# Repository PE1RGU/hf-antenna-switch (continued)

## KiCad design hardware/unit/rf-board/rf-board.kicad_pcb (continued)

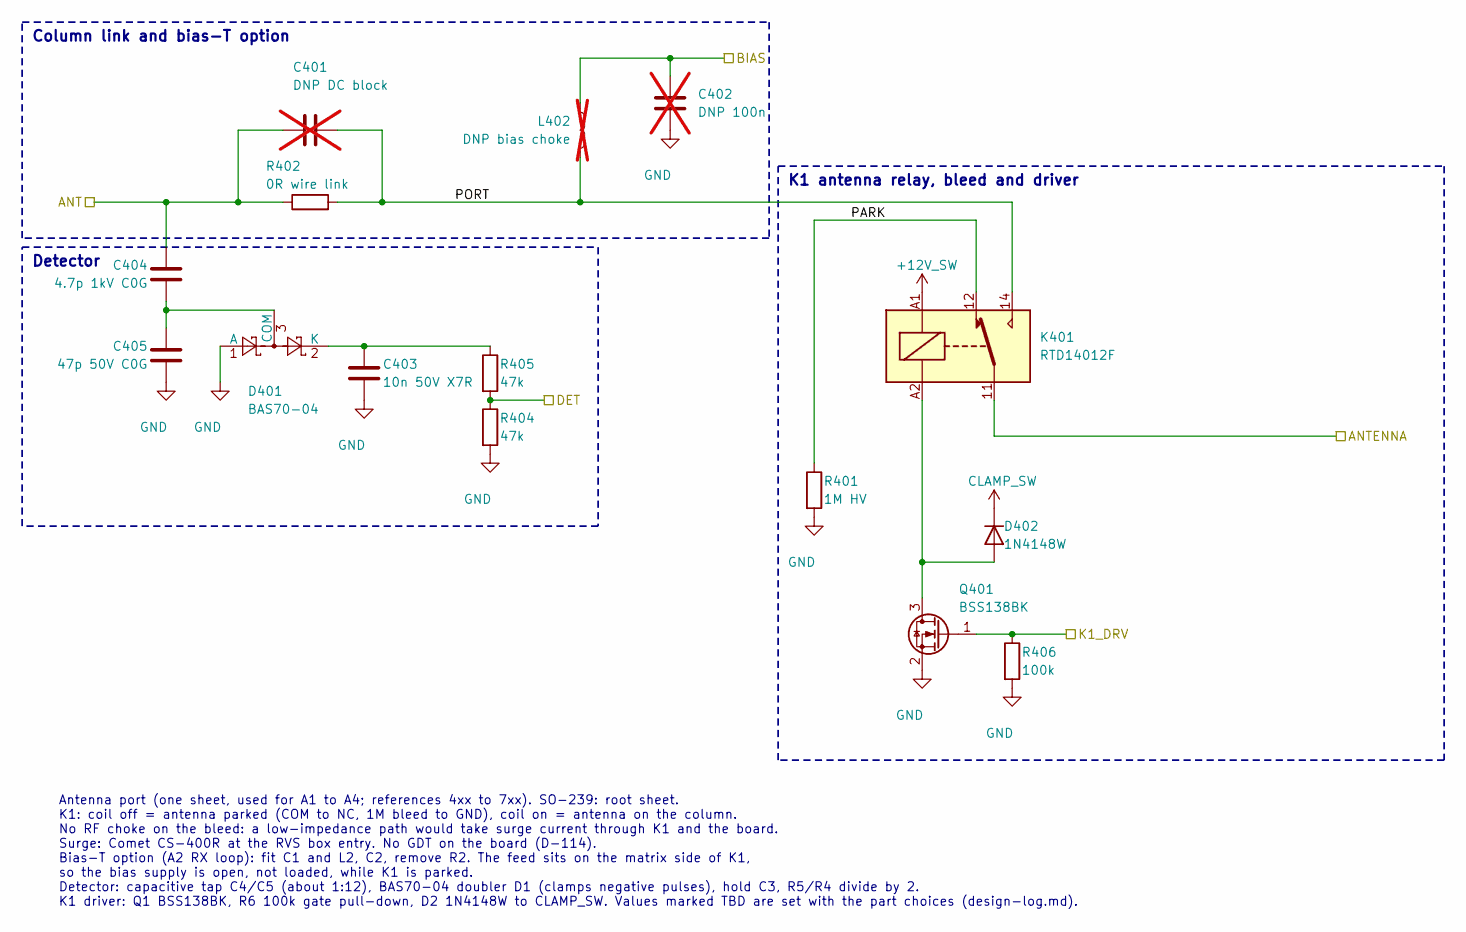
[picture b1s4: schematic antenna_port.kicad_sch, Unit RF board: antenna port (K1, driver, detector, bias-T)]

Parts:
C401: DNP DC block; C_1812_4532Metric_Pad1.57x3.40mm_HandSolder; not fitted
C402: DNP 100n; C_1206_3216Metric_Pad1.33x1.80mm_HandSolder; not fitted
C403: 10n 50V X7R; C_0603_1608Metric_Pad1.08x0.95mm_HandSolder
C404: 4.7p 1kV C0G; C_1206_3216Metric_RFgap2.0; MPN 1206J1K04P70CCT
C405: 47p 50V C0G; C_0603_1608Metric_Pad1.08x0.95mm_HandSolder
D401: BAS70-04; SOT-23; MPN BAS70-04
D402: 1N4148W; D_SOD-123; MPN 1N4148W
K401: RTD14012F; Relay_SPDT_Schrack-RT1-16A-FormC_RM5mm; MPN RTD14012F
L402: DNP bias choke; L_1812_4532Metric_Pad1.30x3.40mm_HandSolder; not fitted
Q401: BSS138BK; SOT-23; MPN BSS138BK,215
R401: 1M HV; R_Axial_DIN0207_L6.3mm_D2.5mm_P10.16mm_Horizontal
R402: 0R wire link; WireLink_P7.62mm_D1.0mm
R404, R405: 47k; R_0603_1608Metric_Pad0.98x0.95mm_HandSolder
R406: 100k; R_0603_1608Metric_Pad0.98x0.95mm_HandSolder

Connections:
+12V_SW: K401.A1; also elsewhere on the board
/A1_ANTENNA: K401.11; also elsewhere on the board
/A1_BIAS: C402.1, L402.1; also elsewhere on the board
/A1_DET: R404.1, R405.2; also elsewhere on the board
/A1_K1_DRV: Q401.1 (G), R406.1; also elsewhere on the board
/ANT1: C401.1, C404.1, R402.1; also elsewhere on the board
/Antenna port A1/PARK: K401.12, R401.1
/Antenna port A1/PORT: C401.2, K401.14, L402.2, R402.2
CLAMP_SW: D402.1 (K); also elsewhere on the board
GND: C402.2, C403.2, C405.2, D401.1 (A), Q401.2 (S), R401.2, R404.2, R406.2; also elsewhere on the board
unnamed: C404.2, C405.1, D401.3 (COM)
unnamed: C403.1, D401.2 (K), R405.1
unnamed: D402.2 (A), K401.A2, Q401.3 (D)

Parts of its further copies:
C501, C601, C701: DNP DC block; C_1812_4532Metric_Pad1.57x3.40mm_HandSolder; not fitted
C502, C602, C702: DNP 100n; C_1206_3216Metric_Pad1.33x1.80mm_HandSolder; not fitted
C503, C603, C703: 10n 50V X7R; C_0603_1608Metric_Pad1.08x0.95mm_HandSolder
C504, C604, C704: 4.7p 1kV C0G; C_1206_3216Metric_RFgap2.0; MPN 1206J1K04P70CCT
C505, C605, C705: 47p 50V C0G; C_0603_1608Metric_Pad1.08x0.95mm_HandSolder
D501, D601, D701: BAS70-04; SOT-23; MPN BAS70-04
D502, D602, D702: 1N4148W; D_SOD-123; MPN 1N4148W
K501, K601, K701: RTD14012F; Relay_SPDT_Schrack-RT1-16A-FormC_RM5mm; MPN RTD14012F
L502, L602, L702: DNP bias choke; L_1812_4532Metric_Pad1.30x3.40mm_HandSolder; not fitted
Q501, Q601, Q701: BSS138BK; SOT-23; MPN BSS138BK,215
R501, R601, R701: 1M HV; R_Axial_DIN0207_L6.3mm_D2.5mm_P10.16mm_Horizontal
R502, R602, R702: 0R wire link; WireLink_P7.62mm_D1.0mm
R504, R505, R604, R605, R704, R705: 47k; R_0603_1608Metric_Pad0.98x0.95mm_HandSolder
R506, R606, R706: 100k; R_0603_1608Metric_Pad0.98x0.95mm_HandSolder

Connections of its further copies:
+12V_SW: K501.A1, K601.A1, K701.A1; also elsewhere on the board
/A2_ANTENNA: K501.11; also elsewhere on the board
/A2_BIAS: C502.1, L502.1; also elsewhere on the board
/A2_DET: R504.1, R505.2; also elsewhere on the board
/A2_K1_DRV: Q501.1 (G), R506.1; also elsewhere on the board
/A3_ANTENNA: K601.11; also elsewhere on the board
/A3_BIAS: C602.1, L602.1; also elsewhere on the board
/A3_DET: R604.1, R605.2; also elsewhere on the board
/A3_K1_DRV: Q601.1 (G), R606.1; also elsewhere on the board
/A4_ANTENNA: K701.11; also elsewhere on the board
/A4_BIAS: C702.1, L702.1; also elsewhere on the board
/A4_DET: R704.1, R705.2; also elsewhere on the board
/A4_K1_DRV: Q701.1 (G), R706.1; also elsewhere on the board
/ANT2: C501.1, C504.1, R502.1; also elsewhere on the board
/ANT3: C601.1, C604.1, R602.1; also elsewhere on the board
/ANT4: C701.1, C704.1, R702.1; also elsewhere on the board
/Antenna port A2/PARK: K501.12, R501.1
/Antenna port A2/PORT: C501.2, K501.14, L502.2, R502.2
/Antenna port A3/PARK: K601.12, R601.1
/Antenna port A3/PORT: C601.2, K601.14, L602.2, R602.2
/Antenna port A4/PARK: K701.12, R701.1
/Antenna port A4/PORT: C701.2, K701.14, L702.2, R702.2
CLAMP_SW: D502.1 (K), D602.1 (K), D702.1 (K); also elsewhere on the board
GND: C502.2, C503.2, C505.2, C602.2, C603.2, C605.2, C702.2, C703.2, C705.2, D501.1 (A), D601.1 (A), D701.1 (A), Q501.2 (S), Q601.2 (S), Q701.2 (S), R501.2, R504.2, R506.2, R601.2, R604.2, R606.2, R701.2, R704.2, R706.2; also elsewhere on the board
unnamed: C504.2, C505.1, D501.3 (COM)
unnamed: C503.1, D501.2 (K), R505.1
unnamed: D502.2 (A), K501.A2, Q501.3 (D)
unnamed: C604.2, C605.1, D601.3 (COM)
unnamed: C603.1, D601.2 (K), R605.1
unnamed: D602.2 (A), K601.A2, Q601.3 (D)
unnamed: C704.2, C705.1, D701.3 (COM)
unnamed: C703.1, D701.2 (K), R705.1
unnamed: D702.2 (A), K701.A2, Q701.3 (D)

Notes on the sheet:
Antenna port (one sheet, used for A1 to A4; references 4xx to 7xx). SO-239: root sheet. K1: coil off = antenna parked (COM to NC, 1M bleed to GND), coil on = antenna on the column. No RF choke on the bleed: a low-impedance path would take surge current through K1 and the board. Surge: Comet CS-400R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
Column link and bias-T option
Detector
K1 antenna relay, bleed and driver

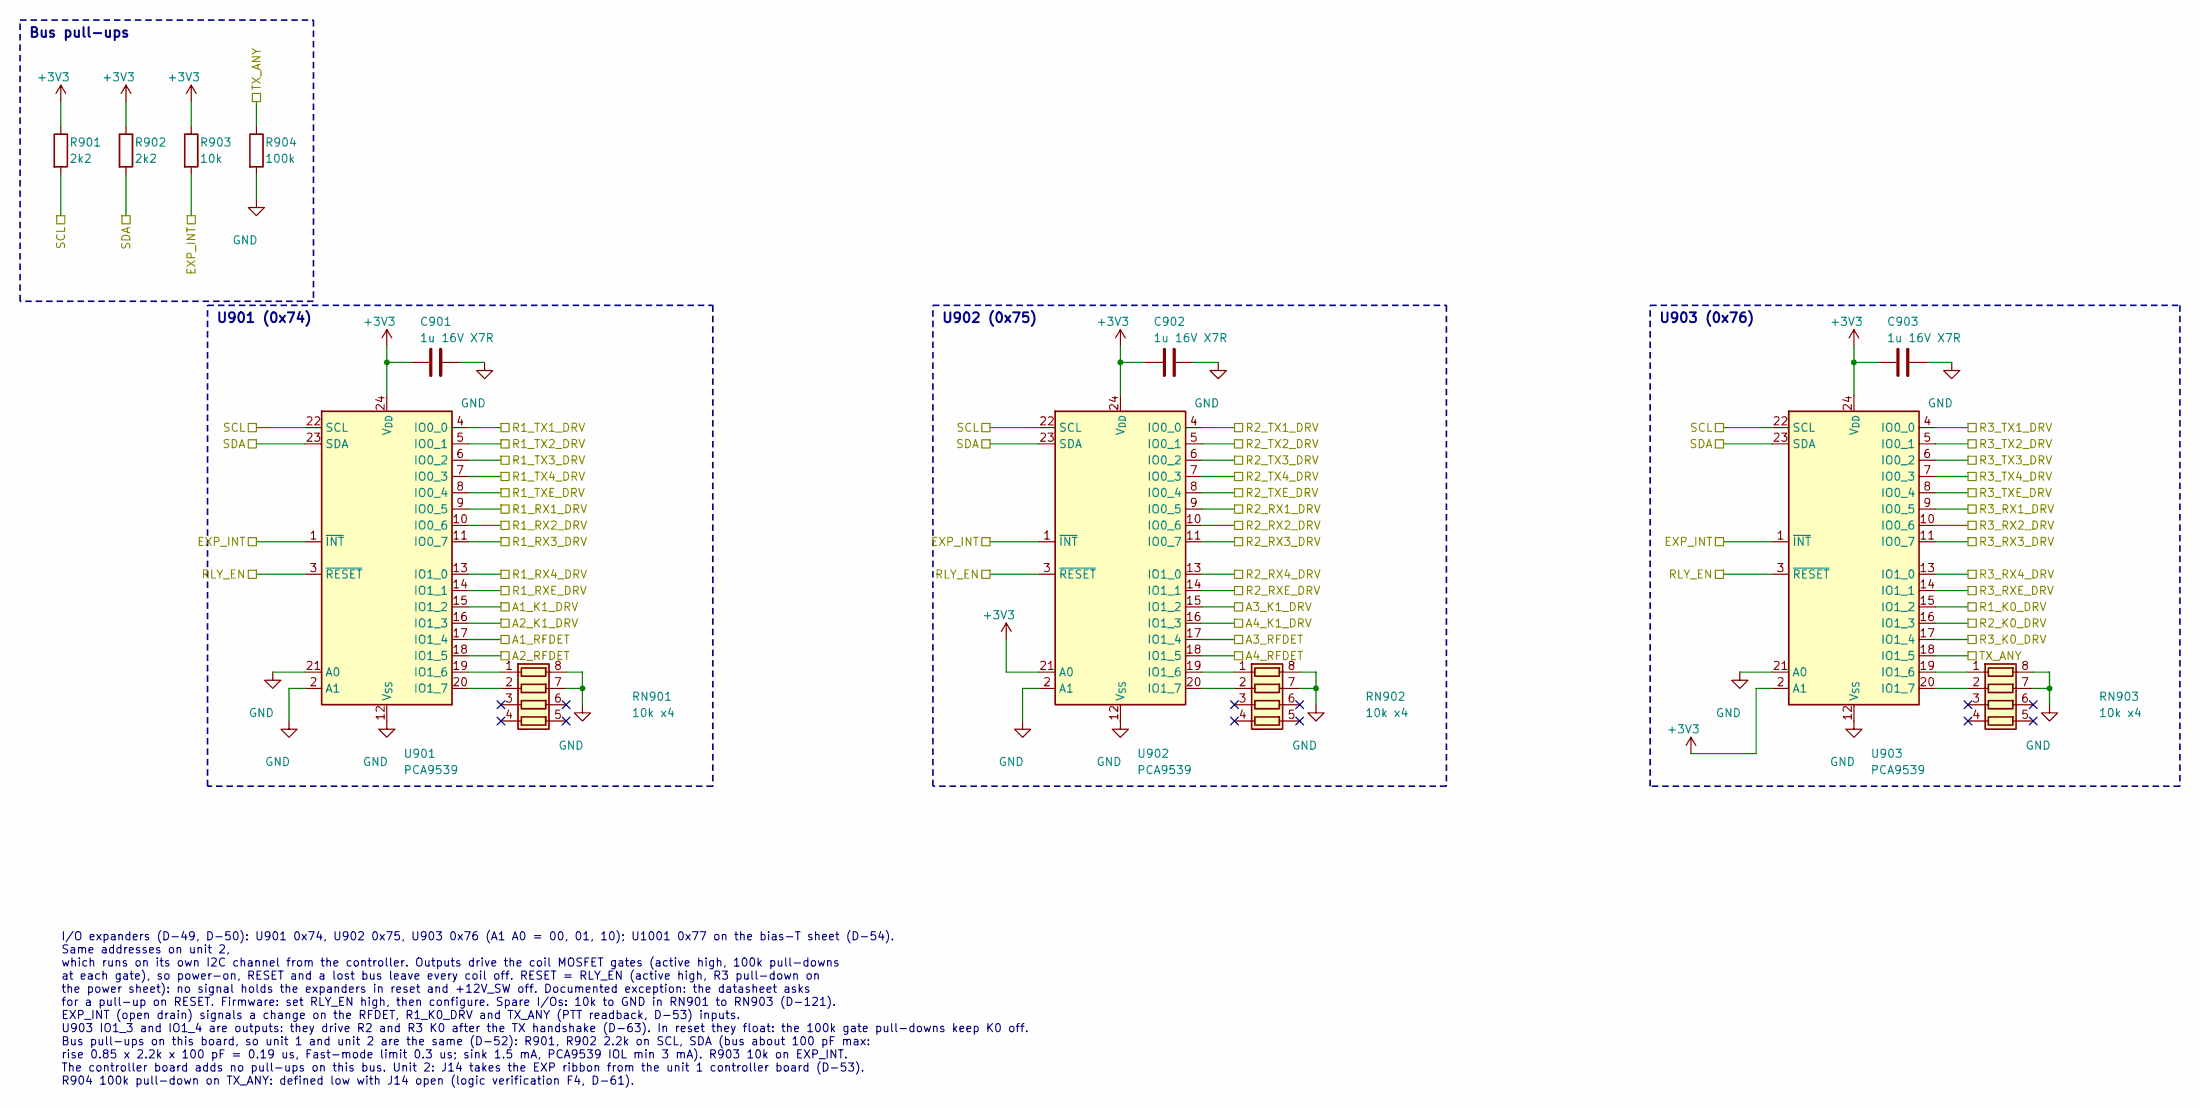
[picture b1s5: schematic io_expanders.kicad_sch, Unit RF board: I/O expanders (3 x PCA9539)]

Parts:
C901, C902, C903: 1u 16V X7R; C_0603_1608Metric_Pad1.08x0.95mm_HandSolder
R901, R902: 2k2; R_0603_1608Metric_Pad0.98x0.95mm_HandSolder
R903: 10k; R_0603_1608Metric_Pad0.98x0.95mm_HandSolder
R904: 100k; R_0603_1608Metric_Pad0.98x0.95mm_HandSolder
RN901, RN902, RN903: 10k x4; R_Array_Convex_4x0603; MPN CAY16-103J4LF
U901, U902, U903: PCA9539; TSSOP-24_4.4x7.8mm_P0.65mm; MPN PCA9539PW,118

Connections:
+3V3: C901.1, C902.1, C903.1, R901.1, R902.1, R903.1, U901.24 (V_{DD}), U902.21 (A0), U902.24 (V_{DD}), U903.2 (A1), U903.24 (V_{DD}); also elsewhere on the board
/A1_K1_DRV: U901.15 (IO1_2); also elsewhere on the board
/A2_K1_DRV: U901.16 (IO1_3); also elsewhere on the board
/A2_RFDET: U901.18 (IO1_5); also elsewhere on the board
/A3_K1_DRV: U902.15 (IO1_2); also elsewhere on the board
/A4_K1_DRV: U902.16 (IO1_3); also elsewhere on the board
/EXP_INT: R903.2, U901.1 (~INT), U902.1 (~INT), U903.1 (~INT); also elsewhere on the board
/IO expanders/A1_RFDET: U901.17 (IO1_4); also elsewhere on the board
/IO expanders/A3_RFDET: U902.17 (IO1_4); also elsewhere on the board
/IO expanders/A4_RFDET: U902.18 (IO1_5); also elsewhere on the board
/R1_K0_DRV: U903.15 (IO1_2); also elsewhere on the board
/R1_RX1_DRV: U901.9 (IO0_5); also elsewhere on the board
/R1_RX2_DRV: U901.10 (IO0_6); also elsewhere on the board
/R1_RX3_DRV: U901.11 (IO0_7); also elsewhere on the board
/R1_RX4_DRV: U901.13 (IO1_0); also elsewhere on the board
/R1_RXE_DRV: U901.14 (IO1_1); also elsewhere on the board
/R1_TX1_DRV: U901.4 (IO0_0); also elsewhere on the board
/R1_TX2_DRV: U901.5 (IO0_1); also elsewhere on the board
/R1_TX3_DRV: U901.6 (IO0_2); also elsewhere on the board
/R1_TX4_DRV: U901.7 (IO0_3); also elsewhere on the board
/R1_TXE_DRV: U901.8 (IO0_4); also elsewhere on the board
/R2_K0_DRV: U903.16 (IO1_3); also elsewhere on the board
/R2_RX1_DRV: U902.9 (IO0_5); also elsewhere on the board
/R2_RX2_DRV: U902.10 (IO0_6); also elsewhere on the board
/R2_RX3_DRV: U902.11 (IO0_7); also elsewhere on the board
/R2_RX4_DRV: U902.13 (IO1_0); also elsewhere on the board
/R2_RXE_DRV: U902.14 (IO1_1); also elsewhere on the board
/R2_TX1_DRV: U902.4 (IO0_0); also elsewhere on the board
/R2_TX2_DRV: U902.5 (IO0_1); also elsewhere on the board
/R2_TX3_DRV: U902.6 (IO0_2); also elsewhere on the board
/R2_TX4_DRV: U902.7 (IO0_3); also elsewhere on the board
/R2_TXE_DRV: U902.8 (IO0_4); also elsewhere on the board
/R3_K0_DRV: U903.17 (IO1_4); also elsewhere on the board
/R3_RX1_DRV: U903.9 (IO0_5); also elsewhere on the board
/R3_RX2_DRV: U903.10 (IO0_6); also elsewhere on the board
/R3_RX3_DRV: U903.11 (IO0_7); also elsewhere on the board
/R3_RX4_DRV: U903.13 (IO1_0); also elsewhere on the board
/R3_RXE_DRV: U903.14 (IO1_1); also elsewhere on the board
/R3_TX1_DRV: U903.4 (IO0_0); also elsewhere on the board
/R3_TX2_DRV: U903.5 (IO0_1); also elsewhere on the board
/R3_TX3_DRV: U903.6 (IO0_2); also elsewhere on the board
/R3_TX4_DRV: U903.7 (IO0_3); also elsewhere on the board
/R3_TXE_DRV: U903.8 (IO0_4); also elsewhere on the board
/RLY_EN: U901.3 (~RESET), U902.3 (~RESET), U903.3 (~RESET); also elsewhere on the board
/SCL: R901.2, U901.22 (SCL), U902.22 (SCL), U903.22 (SCL); also elsewhere on the board
/SDA: R902.2, U901.23 (SDA), U902.23 (SDA), U903.23 (SDA); also elsewhere on the board
/TX_ANY: R904.1, U903.18 (IO1_5); also elsewhere on the board
GND: C901.2, C902.2, C903.2, R904.2, RN901.7 (R2.2), RN901.8 (R1.2), RN902.7 (R2.2), RN902.8 (R1.2), RN903.7 (R2.2), RN903.8 (R1.2), U901.2 (A1), U901.12 (V_{SS}), U901.21 (A0), U902.2 (A1), U902.12 (V_{SS}), U903.12 (V_{SS}), U903.21 (A0); also elsewhere on the board
unnamed: RN901.1 (R1.1), U901.19 (IO1_6)
unnamed: RN901.2 (R2.1), U901.20 (IO1_7)
unnamed: RN902.1 (R1.1), U902.19 (IO1_6)
unnamed: RN902.2 (R2.1), U902.20 (IO1_7)
unnamed: RN903.1 (R1.1), U903.19 (IO1_6)
unnamed: RN903.2 (R2.1), U903.20 (IO1_7)

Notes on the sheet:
I/O expanders (D-49, D-50): U901 0x74, U902 0x75, U903 0x76 (A1 A0 = 00, 01, 10); U1001 0x77 on the bias-T sheet (D-54). Same addresses on unit 2, which runs on its own I2C channel from the controller. Outputs drive the coil MOSFET gates (active high, 100k pull-downs at each gate), so power-on, RES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
Bus pull-ups
U901 (0x74)
U902 (0x75)
U903 (0x76)

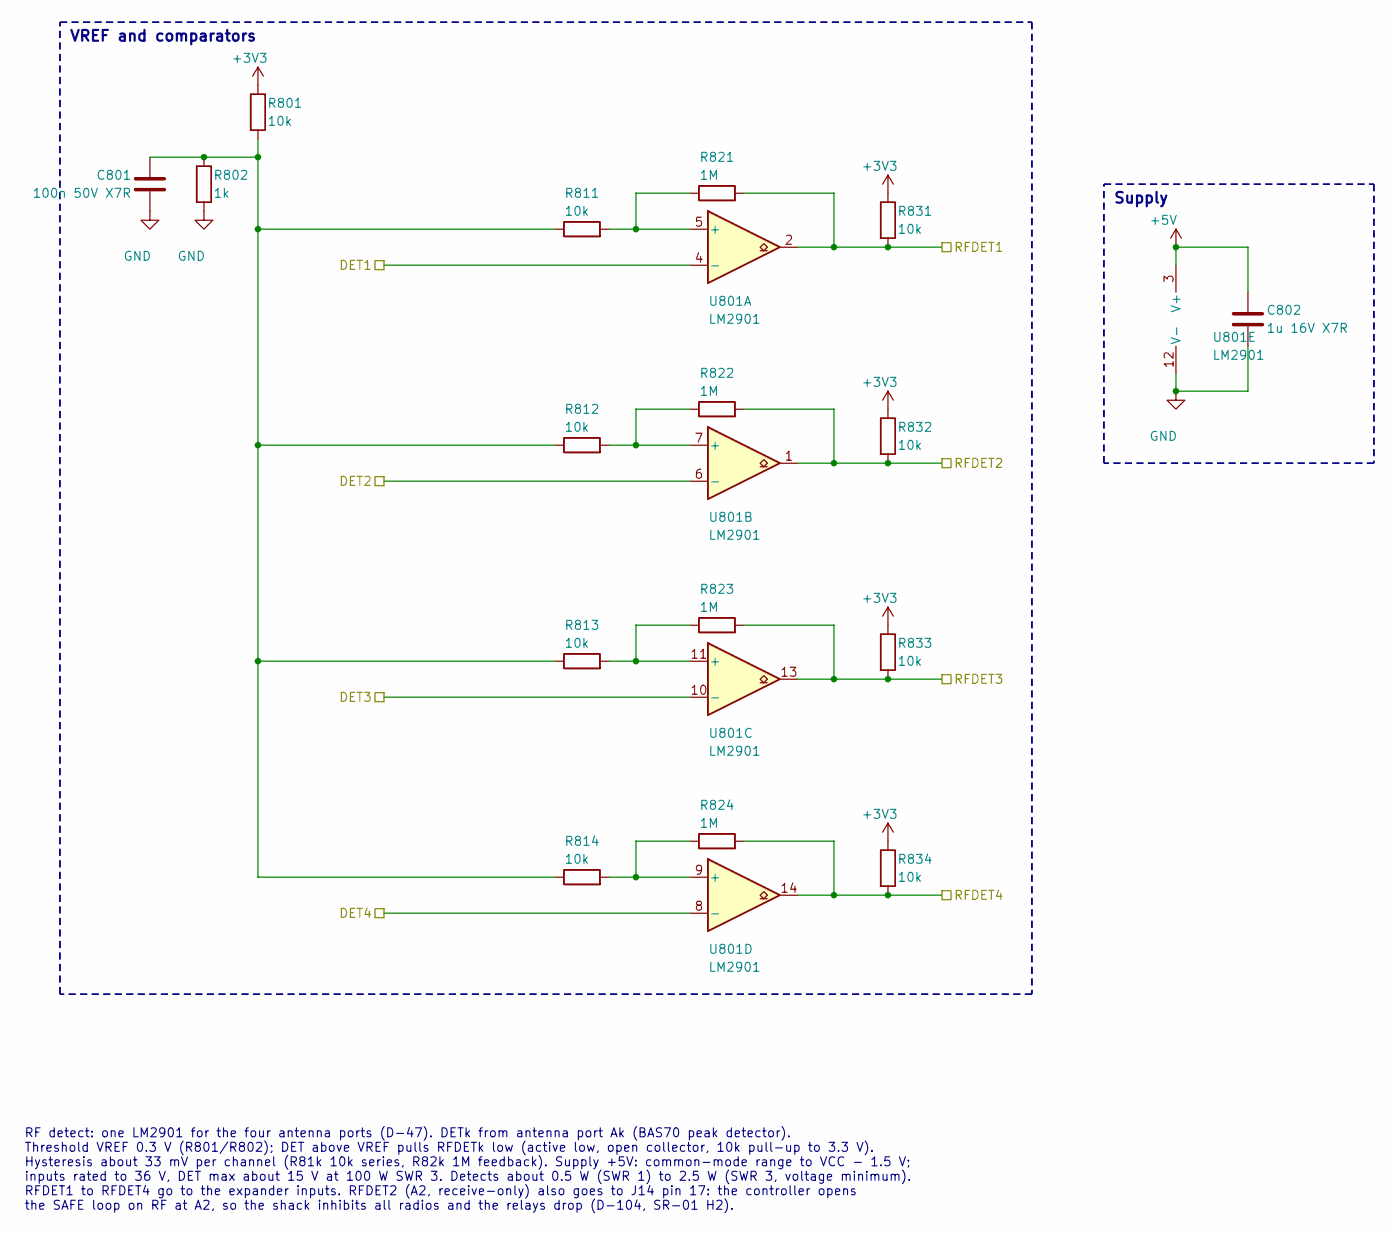
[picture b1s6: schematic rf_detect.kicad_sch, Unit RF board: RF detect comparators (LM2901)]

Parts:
C801: 100n 50V X7R; C_0603_1608Metric_Pad1.08x0.95mm_HandSolder
C802: 1u 16V X7R; C_0603_1608Metric_Pad1.08x0.95mm_HandSolder
R801, R811, R812, R813, R814, R831, R832, R833, R834: 10k; R_0603_1608Metric_Pad0.98x0.95mm_HandSolder
R802: 1k; R_0603_1608Metric_Pad0.98x0.95mm_HandSolder
R821, R822, R823, R824: 1M; R_0603_1608Metric_Pad0.98x0.95mm_HandSolder
U801: LM2901; SOIC-14_3.9x8.7mm_P1.27mm; MPN LM2901DR

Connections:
+3V3: R801.1, R831.1, R832.1, R833.1, R834.1; also elsewhere on the board
+5V: C802.1, U801.3 (V+); also elsewhere on the board
/A1_DET: U801.4 (-); also elsewhere on the board
/A2_DET: U801.6 (-); also elsewhere on the board
/A2_RFDET: R822.2, R832.2, U801.1; also elsewhere on the board
/A3_DET: U801.10 (-); also elsewhere on the board
/A4_DET: U801.8 (-); also elsewhere on the board
/IO expanders/A1_RFDET: R821.2, R831.2, U801.2; also elsewhere on the board
/IO expanders/A3_RFDET: R823.2, R833.2, U801.13; also elsewhere on the board
/IO expanders/A4_RFDET: R824.2, R834.2, U801.14; also elsewhere on the board
GND: C801.2, C802.2, R802.2, U801.12 (V-); also elsewhere on the board
unnamed: C801.1, R801.2, R802.1, R811.1, R812.1, R813.1, R814.1
unnamed: R811.2, R821.1, U801.5 (+)
unnamed: R812.2, R822.1, U801.7 (+)
unnamed: R813.2, R823.1, U801.11 (+)
unnamed: R814.2, R824.1, U801.9 (+)

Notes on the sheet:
RF detect: one LM2901 for the four antenna ports (D-47). DETk from antenna port Ak (BAS70 peak detector). Threshold VREF 0.3 V (R801/R802); DET above VREF pulls RFDETk low (active low, open collector, 10k pull-up to 3.3 V). Hysteresis about 33 mV per channel (R81k 10k series, R82k 1M feedback). Sup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
VREF and comparators
Supply

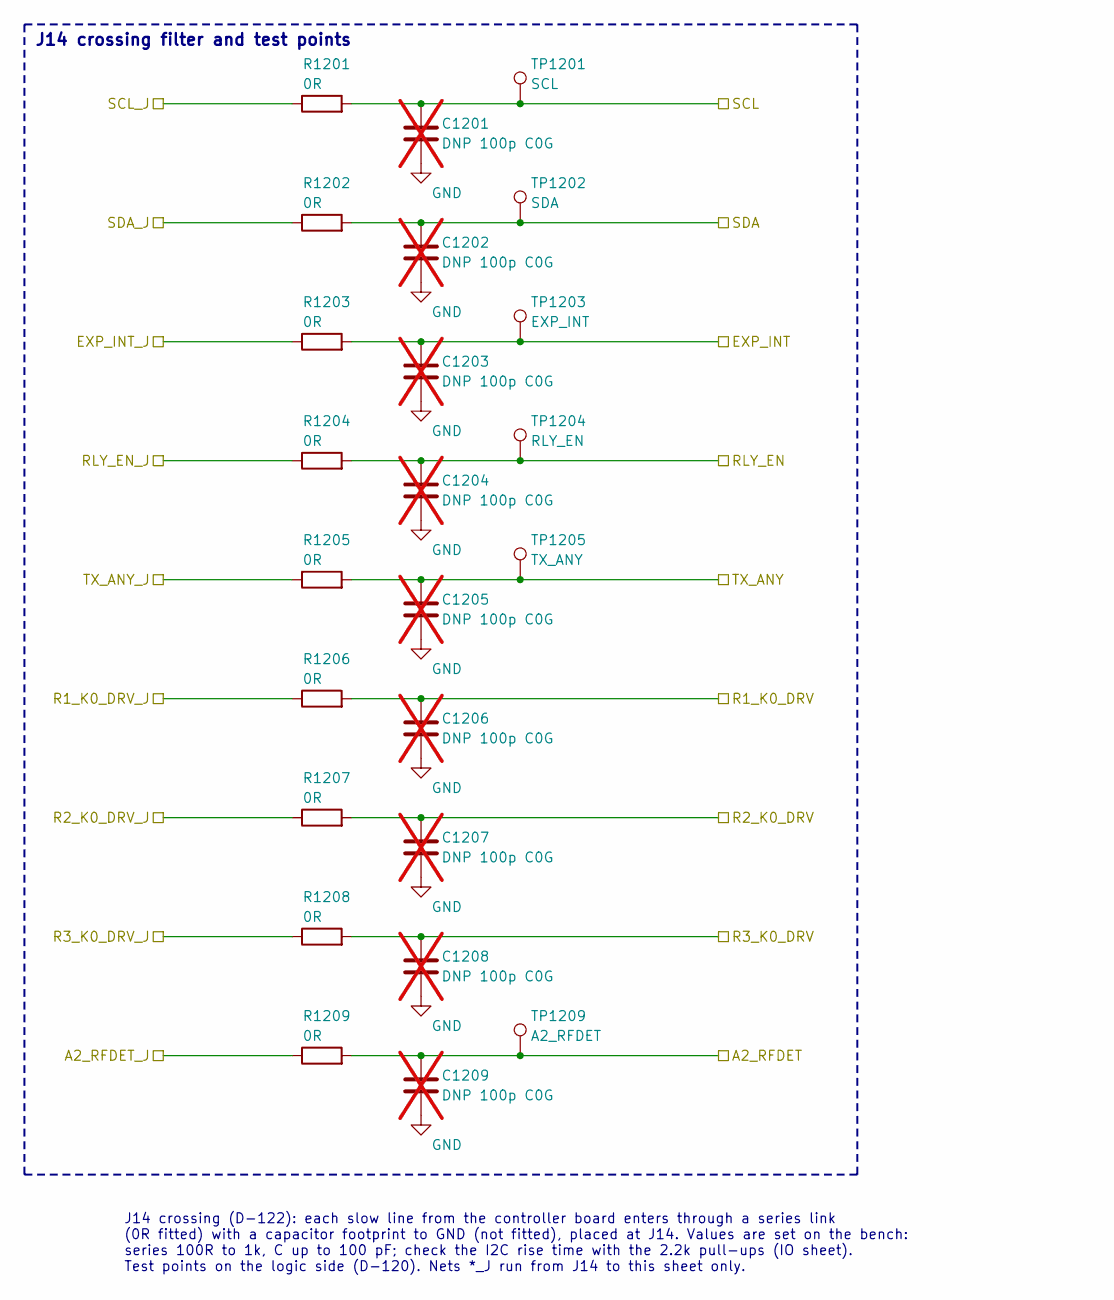
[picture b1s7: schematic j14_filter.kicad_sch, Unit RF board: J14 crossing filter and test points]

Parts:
C1201, C1202, C1203, C1204, C1205, C1206, C1207, C1208, C1209: DNP 100p C0G; C_0603_1608Metric_Pad1.08x0.95mm_HandSolder; not fitted
R1201, R1202, R1203, R1204, R1205, R1206, R1207, R1208, R1209: 0R; R_0603_1608Metric_Pad0.98x0.95mm_HandSolder
TP1201: SCL; TestPoint_Pad_D1.5mm
TP1202: SDA; TestPoint_Pad_D1.5mm
TP1203: EXP_INT; TestPoint_Pad_D1.5mm
TP1204: RLY_EN; TestPoint_Pad_D1.5mm
TP1205: TX_ANY; TestPoint_Pad_D1.5mm
TP1209: A2_RFDET; TestPoint_Pad_D1.5mm

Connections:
/A2_RFDET: C1209.1, R1209.2, TP1209.1; also elsewhere on the board
/A2_RFDET_J: R1209.1; also elsewhere on the board
/EXP_INT: C1203.1, R1203.2, TP1203.1; also elsewhere on the board
/EXP_INT_J: R1203.1; also elsewhere on the board
/R1_K0_DRV: C1206.1, R1206.2; also elsewhere on the board
/R1_K0_DRV_J: R1206.1; also elsewhere on the board
/R2_K0_DRV: C1207.1, R1207.2; also elsewhere on the board
/R2_K0_DRV_J: R1207.1; also elsewhere on the board
/R3_K0_DRV: C1208.1, R1208.2; also elsewhere on the board
/R3_K0_DRV_J: R1208.1; also elsewhere on the board
/RLY_EN: C1204.1, R1204.2, TP1204.1; also elsewhere on the board
/RLY_EN_J: R1204.1; also elsewhere on the board
/SCL: C1201.1, R1201.2, TP1201.1; also elsewhere on the board
/SCL_J: R1201.1; also elsewhere on the board
/SDA: C1202.1, R1202.2, TP1202.1; also elsewhere on the board
/SDA_J: R1202.1; also elsewhere on the board
/TX_ANY: C1205.1, R1205.2, TP1205.1; also elsewhere on the board
/TX_ANY_J: R1205.1; also elsewhere on the board
GND: C1201.2, C1202.2, C1203.2, C1204.2, C1205.2, C1206.2, C1207.2, C1208.2, C1209.2; also elsewhere on the board

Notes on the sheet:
J14 crossing (D-122): each slow line from the controller board enters through a series link (0R fitted) with a capacitor footprint to GND (not fitted), placed at J14. Values are set on the bench: series 100R to 1k, C up to 100 pF; check the I2C rise time with the 2.2k pull-ups (IO sheet). Test poin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
J14 crossing filter and test points

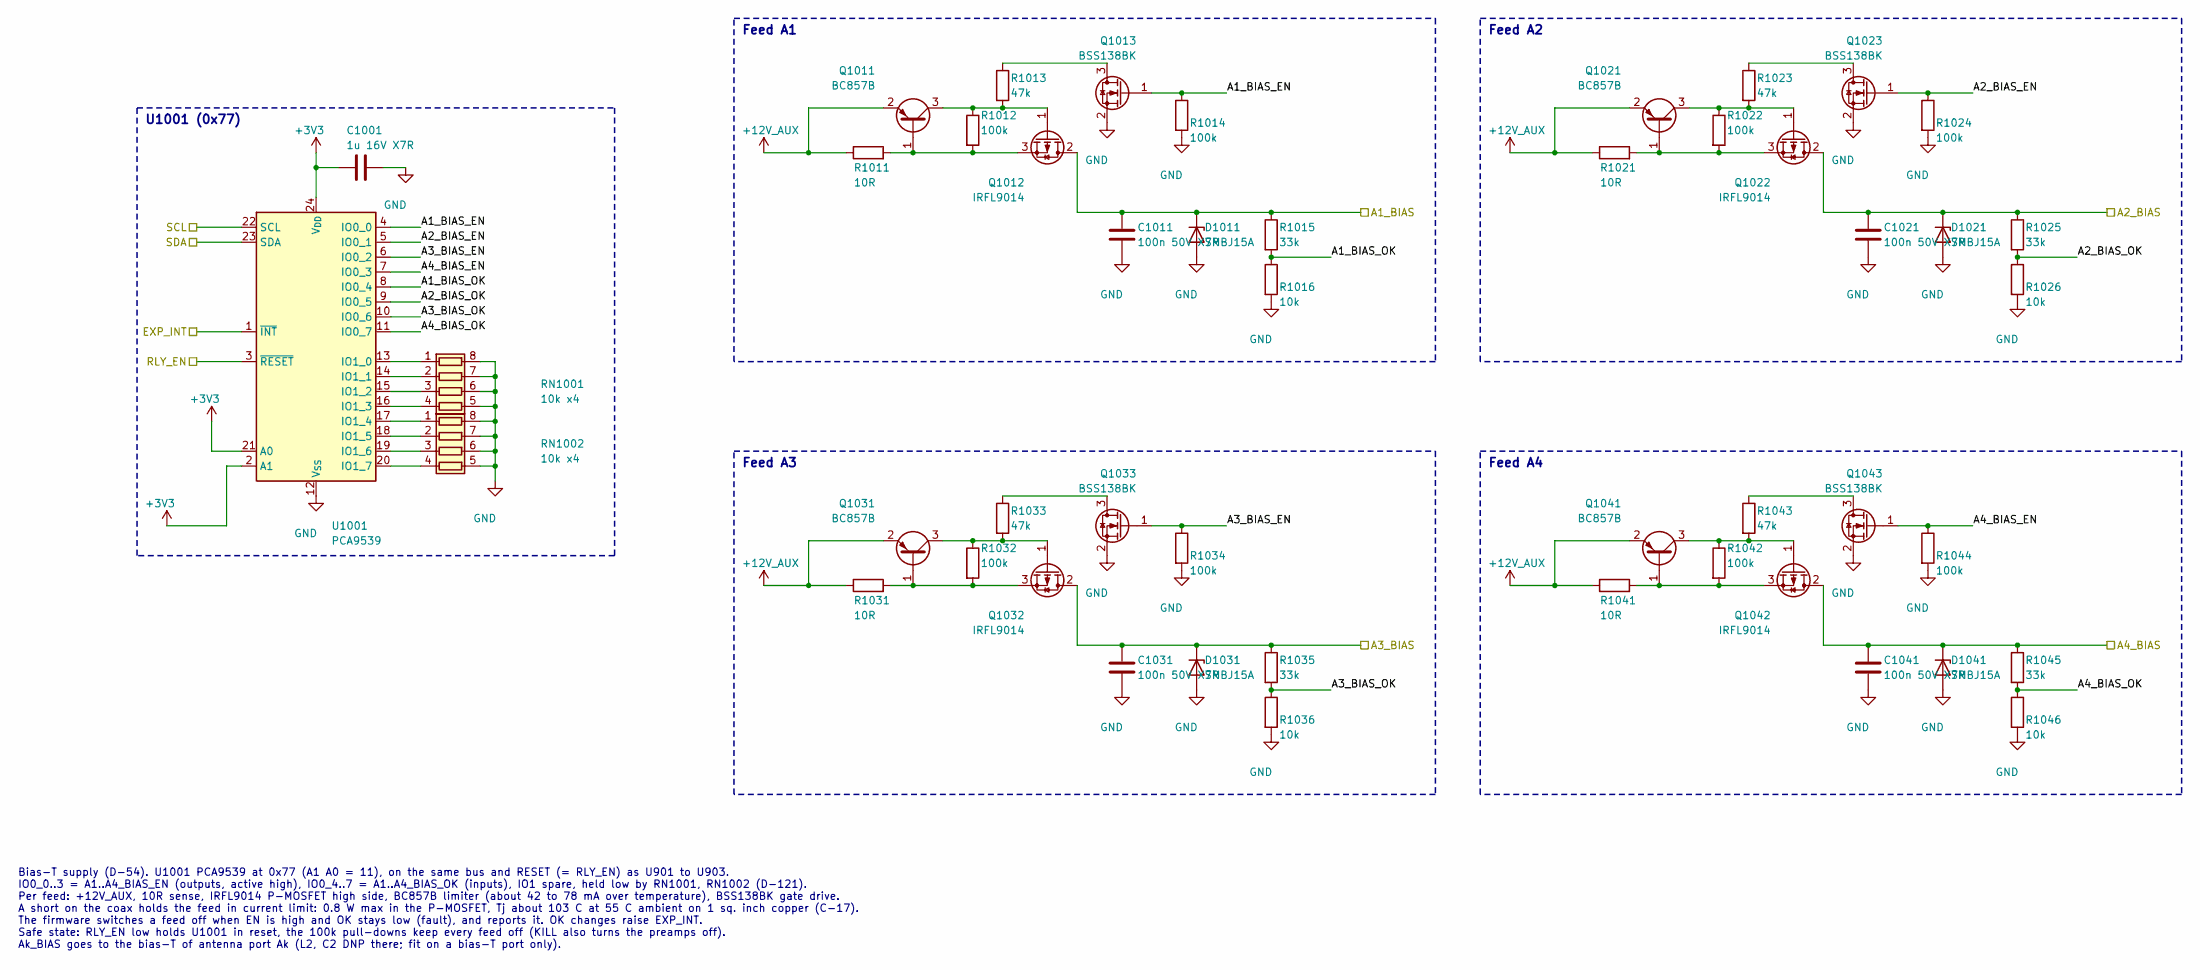
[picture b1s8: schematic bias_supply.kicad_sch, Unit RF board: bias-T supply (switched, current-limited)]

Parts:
C1001: 1u 16V X7R; C_0603_1608Metric_Pad1.08x0.95mm_HandSolder
C1011, C1021, C1031, C1041: 100n 50V X7R; C_0603_1608Metric_Pad1.08x0.95mm_HandSolder
D1011, D1021, D1031, D1041: SMBJ15A; D_SMB; MPN SMBJ15A
Q1011, Q1021, Q1031, Q1041: BC857B; SOT-23; MPN BC857B
Q1012, Q1022, Q1032, Q1042: IRFL9014; SOT-223-3_TabPin2; MPN IRFL9014TRPBF-BE3
Q1013, Q1023, Q1033, Q1043: BSS138BK; SOT-23; MPN BSS138BK,215
R1011, R1021, R1031, R1041: 10R; R_0805_2012Metric_Pad1.20x1.40mm_HandSolder
R1012, R1014, R1022, R1024, R1032, R1034, R1042, R1044: 100k; R_0603_1608Metric_Pad0.98x0.95mm_HandSolder
R1013, R1023, R1033, R1043: 47k; R_0603_1608Metric_Pad0.98x0.95mm_HandSolder
R1015, R1025, R1035, R1045: 33k; R_0603_1608Metric_Pad0.98x0.95mm_HandSolder
R1016, R1026, R1036, R1046: 10k; R_0603_1608Metric_Pad0.98x0.95mm_HandSolder
RN1001, RN1002: 10k x4; R_Array_Convex_4x0603; MPN CAY16-103J4LF
U1001: PCA9539; TSSOP-24_4.4x7.8mm_P0.65mm; MPN PCA9539PW,118

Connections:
+3V3: C1001.1, U1001.2 (A1), U1001.21 (A0), U1001.24 (V_{DD}); also elsewhere on the board
+12V_AUX: Q1011.2 (E), Q1021.2 (E), Q1031.2 (E), Q1041.2 (E), R1011.1, R1021.1, R1031.1, R1041.1; also elsewhere on the board
/A1_BIAS: C1011.1, D1011.1 (K), Q1012.2 (D), R1015.1; also elsewhere on the board
/A2_BIAS: C1021.1, D1021.1 (K), Q1022.2 (D), R1025.1; also elsewhere on the board
/A3_BIAS: C1031.1, D1031.1 (K), Q1032.2 (D), R1035.1; also elsewhere on the board
/A4_BIAS: C1041.1, D1041.1 (K), Q1042.2 (D), R1045.1; also elsewhere on the board
/Bias-T supply/A1_BIAS_EN: Q1013.1 (G), R1014.1, U1001.4 (IO0_0)
/Bias-T supply/A1_BIAS_OK: R1015.2, R1016.1, U1001.8 (IO0_4)
/Bias-T supply/A2_BIAS_EN: Q1023.1 (G), R1024.1, U1001.5 (IO0_1)
/Bias-T supply/A2_BIAS_OK: R1025.2, R1026.1, U1001.9 (IO0_5)
/Bias-T supply/A3_BIAS_EN: Q1033.1 (G), R1034.1, U1001.6 (IO0_2)
/Bias-T supply/A3_BIAS_OK: R1035.2, R1036.1, U1001.10 (IO0_6)
/Bias-T supply/A4_BIAS_EN: Q1043.1 (G), R1044.1, U1001.7 (IO0_3)
/Bias-T supply/A4_BIAS_OK: R1045.2, R1046.1, U1001.11 (IO0_7)
/EXP_INT: U1001.1 (~INT); also elsewhere on the board
/RLY_EN: U1001.3 (~RESET); also elsewhere on the board
/SCL: U1001.22 (SCL); also elsewhere on the board
/SDA: U1001.23 (SDA); also elsewhere on the board
GND: C1001.2, C1011.2, C1021.2, C1031.2, C1041.2, D1011.2 (A), D1021.2 (A), D1031.2 (A), D1041.2 (A), Q1013.2 (S), Q1023.2 (S), Q1033.2 (S), Q1043.2 (S), R1014.2, R1016.2, R1024.2, R1026.2, R1034.2, R1036.2, R1044.2, R1046.2, RN1001.5 (R4.2), RN1001.6 (R3.2), RN1001.7 (R2.2), RN1001.8 (R1.2), RN1002.5 (R4.2), RN1002.6 (R3.2), RN1002.7 (R2.2), RN1002.8 (R1.2), U1001.12 (V_{SS}); also elsewhere on the board
unnamed: Q1011.1 (B), Q1012.3 (S), R1011.2, R1012.2
unnamed: Q1011.3 (C), Q1012.1 (G), R1012.1, R1013.2
unnamed: Q1013.3 (D), R1013.1
unnamed: Q1021.1 (B), Q1022.3 (S), R1021.2, R1022.2
unnamed: Q1021.3 (C), Q1022.1 (G), R1022.1, R1023.2
unnamed: Q1023.3 (D), R1023.1
unnamed: Q1031.1 (B), Q1032.3 (S), R1031.2, R1032.2
unnamed: Q1031.3 (C), Q1032.1 (G), R1032.1, R1033.2
unnamed: Q1033.3 (D), R1033.1
unnamed: Q1041.1 (B), Q1042.3 (S), R1041.2, R1042.2
unnamed: Q1041.3 (C), Q1042.1 (G), R1042.1, R1043.2
unnamed: Q1043.3 (D), R1043.1
unnamed: RN1001.1 (R1.1), U1001.13 (IO1_0)
unnamed: RN1001.2 (R2.1), U1001.14 (IO1_1)
unnamed: RN1001.3 (R3.1), U1001.15 (IO1_2)
unnamed: RN1001.4 (R4.1), U1001.16 (IO1_3)
unnamed: RN1002.1 (R1.1), U1001.17 (IO1_4)
unnamed: RN1002.2 (R2.1), U1001.18 (IO1_5)
unnamed: RN1002.3 (R3.1), U1001.19 (IO1_6)
unnamed: RN1002.4 (R4.1), U1001.20 (IO1_7)

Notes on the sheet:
Bias-T supply (D-54). U1001 PCA9539 at 0x77 (A1 A0 = 11), on the same bus and RESET (= RLY_EN) as U901 to U903. IO0_0..3 = A1..A4_BIAS_EN (outputs, active high), IO0_4..7 = A1..A4_BIAS_OK (inputs), IO1 spare, held low by RN1001, RN1002 (D-121). Per feed: +12V_AUX, 10R sense, IRFL9014 P-MOSFET high 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
U1001 (0x77)
Feed A1
Feed A2
Feed A3
Feed A4
